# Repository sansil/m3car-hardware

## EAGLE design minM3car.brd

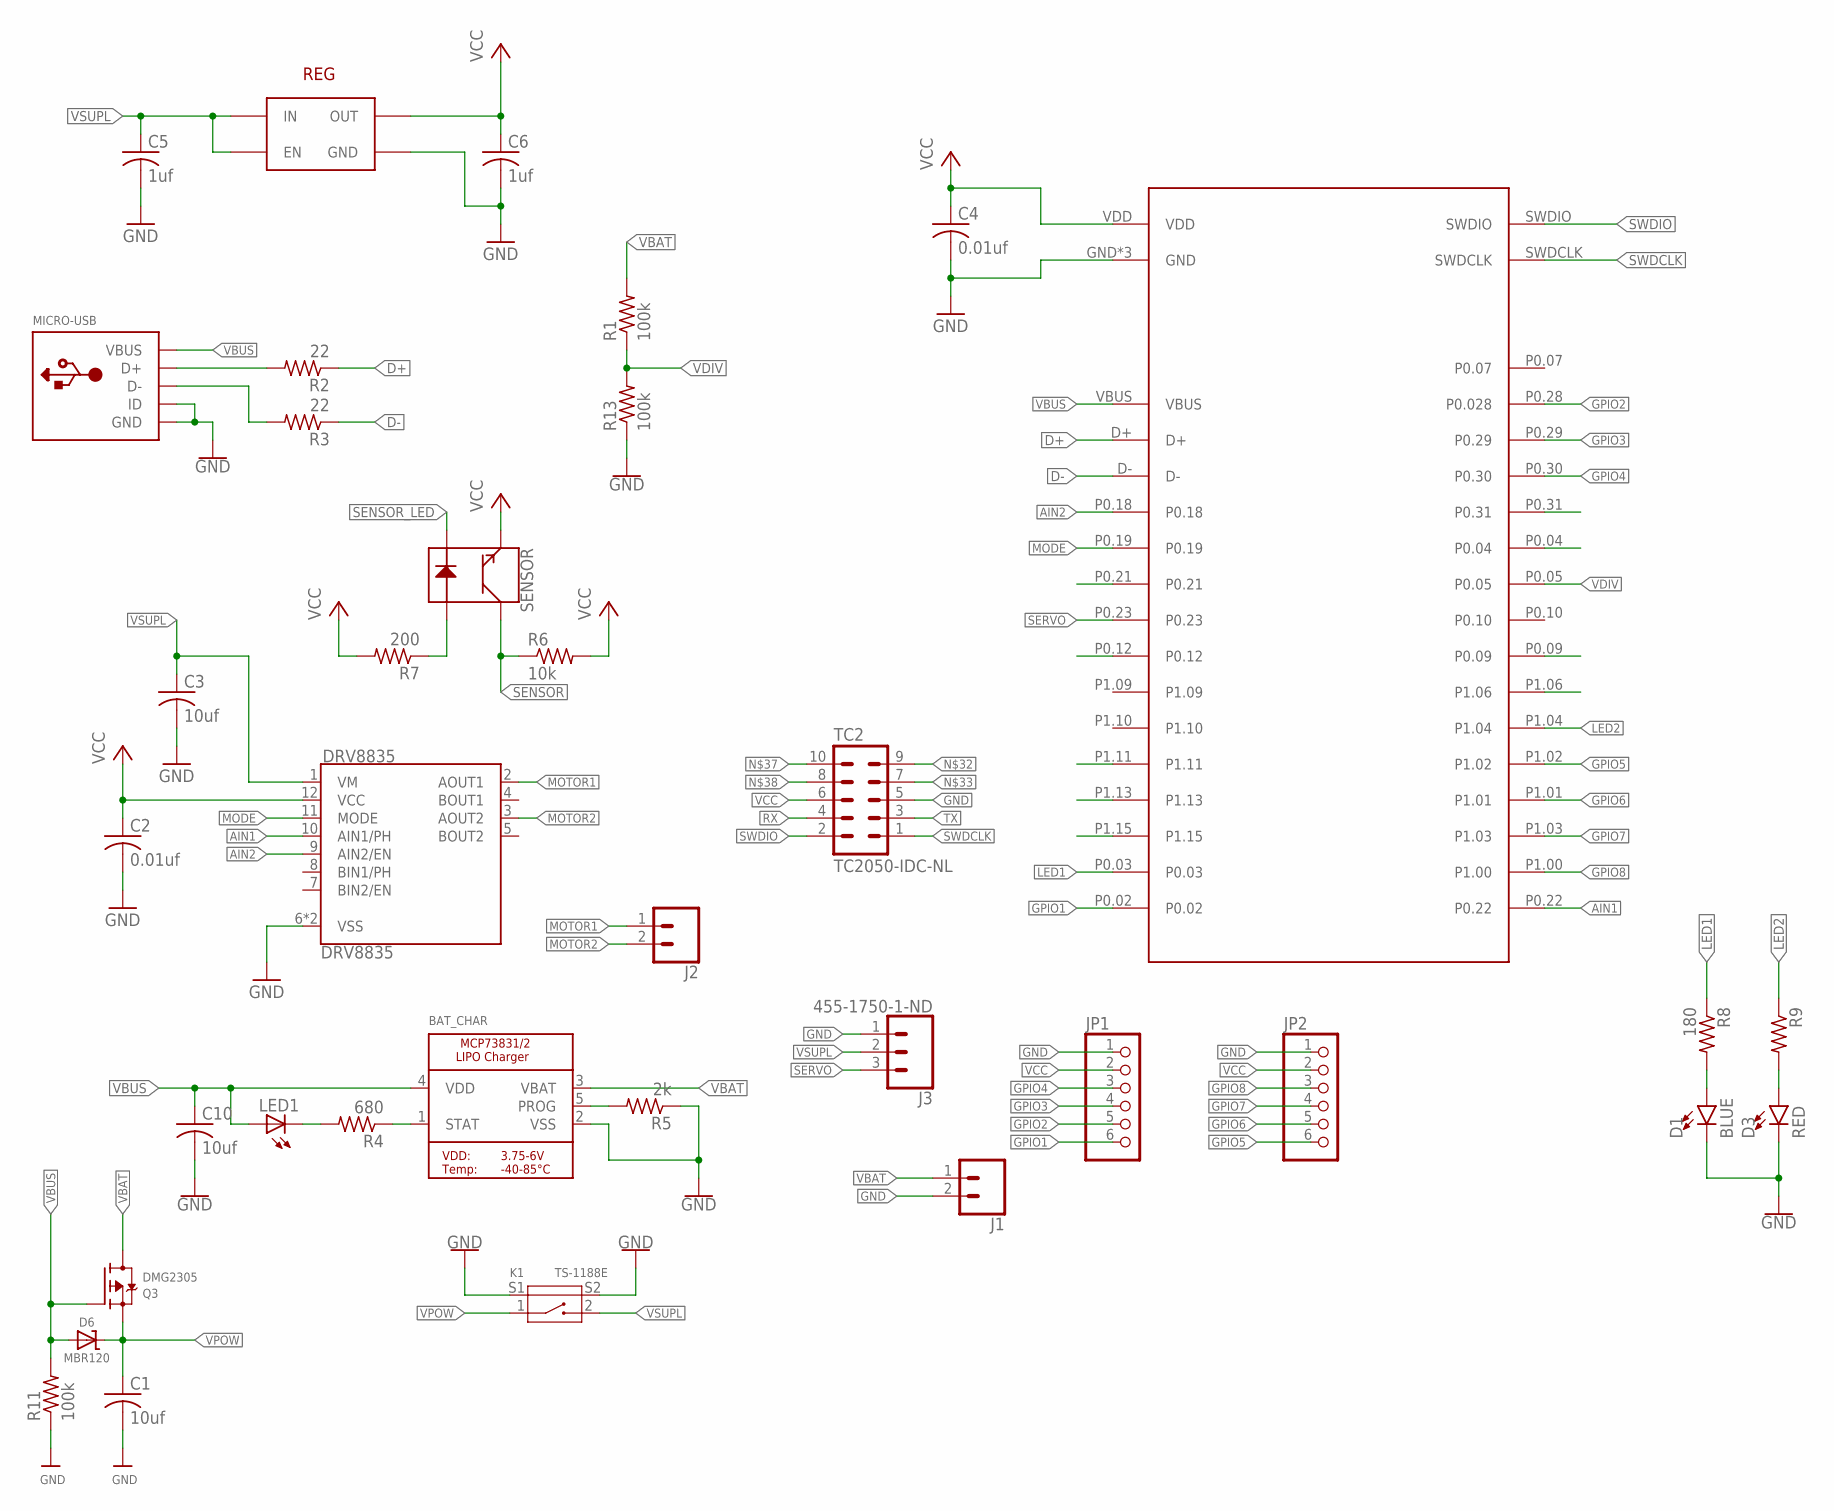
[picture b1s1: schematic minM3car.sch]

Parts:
BAT_CHAR: MICROBUILDER_MCP73831/2; MICROBUILDER_SOT23-5; MPN MCP73831T-2ACI/OT
C1, C3, C10: 10uf; C0402; MPN GRM155R60G106ME44D
C2, C4: 0.01uf; C0402; MPN CL05C100JB5NNNC
C5, C6: 1uf; C0402; MPN CL05A105KP5NNNC
D1: BLUE; LED-0603; MPN 150060YS75000
D3: RED; LED-0603; MPN 150060YS75000
D6: MBR120; SOD-123; MPN MBR120VLSFT3G
DRV8835: DRV8835; WSON-12; MPN DRV8835DSSR
J1, J2: CONN_02; 1X02
J3: 455-1750-1-ND; 1X03
JP1, JP2: PINHD-1X6; 1X06
K1: TS-1188E; SW4-SMD-7.0X3.5X3.5MM-90D
LED1: LEDCHIPLED_0603; CHIPLED_0603; MPN 150060GS75000
MICRO-USB: MICROBUILDER_USB_MICRO_20329_V2; MICROBUILDER_4UCONN_20329_V2; MPN 10103592-0001LF
NRF52: HOLYIOT; MPN 113990556
Q3: DMG2305; SOT23-R; MPN DMG2305UXQ-7
R1, R11, R13: 100k; R0402; MPN RC0402JR-07100KL
R2, R3: 22; R0402; MPN BLM15BB220SN1D
R4: 680; R0402; MPN RC0402JR-07680RL
R5: 2k; R0402; MPN RC0402FR-072KL
R6: 10k; R0402; MPN RC0402JR-0710KL
R7: 200; R0402; MPN 0402WGF2000TCE
R8, R9: 180; R0402; MPN RC0402FR-07180RL
REG: TLV703; SOT95P285X120-5N; MPN TLV7031DBVR
SENSOR: QRE1113SMD-W; QRE1113-W; MPN QRE1113GR
TC2: TC2050-IDC-NL

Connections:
AIN1: DRV8835.10 (AIN1/PH), NRF52.P0.22
AIN2: DRV8835.9 (AIN2/EN), NRF52.P0.18
D+: NRF52.D+, R2.1
D-: NRF52.D-, R3.1
GND: BAT_CHAR.2 (VSS), C1.2, C2.2, C3.2, C4.2, C5.2, C6.2, C10.2, D1.C, D3.C, DRV8835.6 (VSS), DRV8835.PAD (VSS), J1.2, J3.1, JP1.1, JP2.1, K1.S1, K1.S2, MICRO-USB.BASE@1 (GND), MICRO-USB.BASE@2 (GND), MICRO-USB.GND, MICRO-USB.ID, MICRO-USB.SPRT@1 (GND), MICRO-USB.SPRT@2 (GND), MICRO-USB.SPRT@3 (GND), MICRO-USB.SPRT@4 (GND), NRF52.GND, NRF52.GND2 (GND), NRF52.GND3 (GND), R5.1, R11.1, R13.1, REG.2 (GND), TC2.5
GPIO1: JP1.6, NRF52.P0.02
GPIO2: JP1.5, NRF52.P0.28 (P0.028)
GPIO3: JP1.4, NRF52.P0.29
GPIO4: JP1.3, NRF52.P0.30
GPIO5: JP2.6, NRF52.P1.02
GPIO6: JP2.5, NRF52.P1.01
GPIO7: JP2.4, NRF52.P1.03
GPIO8: JP2.3, NRF52.P1.00
LED1: NRF52.P0.03, R8.1
LED2: NRF52.P1.04, R9.1
MODE: DRV8835.11 (MODE), NRF52.P0.19
MOTOR1: DRV8835.2 (AOUT1), J2.1
MOTOR2: DRV8835.3 (AOUT2), J2.2
unnamed: D1.A, R8.2
unnamed: LED1.C, R4.2
unnamed: D3.A, R9.2
unnamed: MICRO-USB.D+, R2.2
unnamed: MICRO-USB.D-, R3.2
unnamed: R7.1, SENSOR.1 (A)
unnamed: BAT_CHAR.5 (PROG), R5.2
unnamed: BAT_CHAR.1 (STAT), R4.1
RX: TC2.4
SENSOR: R6.1, SENSOR.3 (C)
SENSOR_LED: SENSOR.2 (K)
SERVO: J3.3, NRF52.P0.23
SWDCLK: NRF52.SWDCLK, TC2.1
SWDIO: NRF52.SWDIO, TC2.2
TX: TC2.3
VBAT: BAT_CHAR.3 (VBAT), J1.1, Q3.3 (D), R1.2
VBUS: BAT_CHAR.4 (VDD), C10.1, D6.A, LED1.A, MICRO-USB.VBUS, NRF52.VBUS, Q3.1 (G), R11.2
VCC: C2.1, C4.1, C6.1, DRV8835.12 (VCC), JP1.2, JP2.2, NRF52.VDD, R6.2, R7.2, REG.5 (OUT), SENSOR.4 (E), TC2.6
VDIV: NRF52.P0.05, R1.1, R13.2
VPOW: C1.1, D6.C, K1.1, Q3.2 (S)
VSUPL: C3.1, C5.1, DRV8835.1 (VM), J3.2, K1.2, REG.1 (IN), REG.3 (EN)

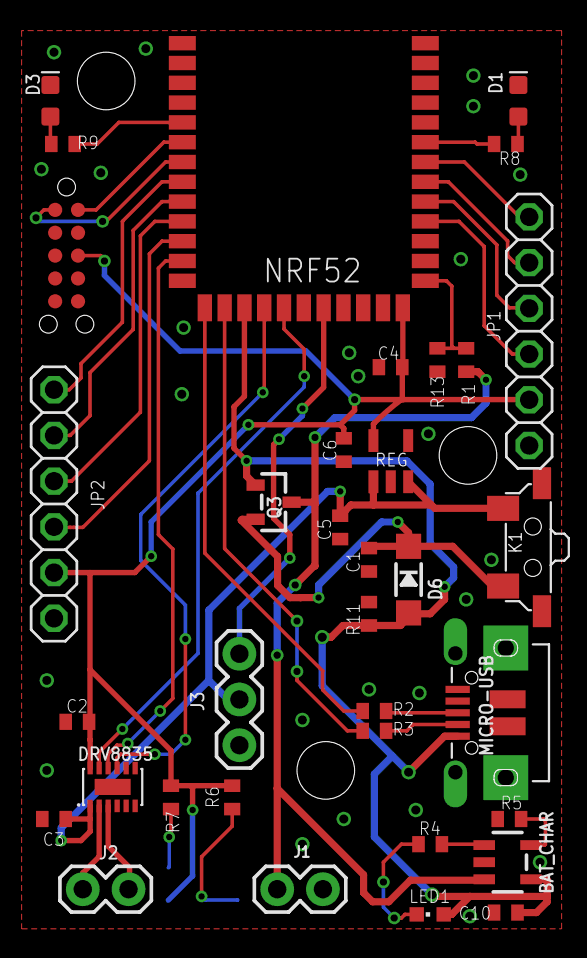
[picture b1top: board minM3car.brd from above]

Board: 2 copper layers, 36 parts (1 on the bottom side), 36 nets.

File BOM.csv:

"Qty";"Value";"Device";"Package";"Parts";"Description";"LINK";"MPN";"PROD_ID";"SF_ID";"VALUE";
"2";"";"CONN_02";"1X02";"J1, J2";"Multi connection point. Often used as Generic Header-pin footprint for 0.1 inch spaced/style header connections";"";"";"";"";"";
"1";"";"LEDCHIPLED_0603";"CHIPLED_0603";"LED1";"LED";"";"150060GS75000";"";"";"";
"1";"";"MICROBUILDER_MCP73831/2";"MICROBUILDER_SOT23-5";"BAT_CHAR";"MCP73831/2 LIPO Charger";"https://uy.mouser.com/ProductDetail/Microchip-Technology/MCP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";" MCP73831T-2ACI/OT";"";"";"";
"1";"";"MICROBUILDER_USB_MICRO_20329_V2";"MICROBUILDER_4UCONN_20329_V2";"MICRO-USB";"USB Connectors";"https://www.digikey.com/product-detail/en/amphenol-icc-fci/1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";"10103592-0001LF ";"";"";"";
"2";"";"PINHD-1X6";"1X06";"JP1, JP2";"PIN HEADER";"";"";"";"";"";
"1";"";"QRE1113SMD-W";"QRE1113-W";"SENSOR";"QRE1113 Reflective Object Sensor";"https://uy.mouser.com/ProductDetail/ON-Semiconductor-Fairchi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";"QRE1113GR";"IC-09357";"COM-09542";"";
"2";"0.01uf";"C-USC0402";"C0402";"C2, C4";"CAPACITOR, American symbol";"";"CL05C100JB5NNNC";"";"";"";
"3";"100k";"R-US_R0402";"R0402";"R1, R11, R13";"RESISTOR, American symbol";"";"RC0402JR-07100KL";"";"";"";
"1";"10k";"R-US_R0402";"R0402";"R6";"RESISTOR, American symbol";"https://www.seeedstudio.com/opl.html";"RC0402JR-0710KL";"";"";"";
"3";"10uf";"C-USC0402";"C0402";"C1, C3, C10";"CAPACITOR, American symbol";"";"GRM155R60G106ME44D";"";"";"";
"2";"180";"R-US_R0402";"R0402";"R8, R9";"RESISTOR, American symbol";"https://www.seeedstudio.com/opl.html";"RC0402FR-07180RL";"";"";"";
"2";"1uf";"C-USC0402";"C0402";"C5, C6";"CAPACITOR, American symbol";"";"CL05A105KP5NNNC";"";"";"";
"1";"200";"R-US_R0402";"R0402";"R7";"RESISTOR, American symbol";"";"0402WGF2000TCE";"";"";"";
"2";"22";"R-US_R0402";"R0402";"R2, R3";"RESISTOR, American symbol";"https://www.seeedstudio.com/opl.html";"BLM15BB220SN1D";"";"";"";
"1";"2k";"R-US_R0402";"R0402";"R5";"RESISTOR, American symbol";"";"RC0402FR-072KL";"";"";"";
"1";"455-1750-1-ND";"CONN_03";"1X03";"J3";"Multi connection point. Often used as Generic Header-pin footprint for 0.1 inch spaced/style header connections";"";"";"XXX-00000";"";"455-1750-1-ND";
"1";"680";"R-US_R0402";"R0402";"R4";"RESISTOR, American symbol";"https://www.seeedstudio.com/opl.html";"RC0402JR-07680RL";"";"";"";
"1";"BLUE";"LED-BLUE0603";"LED-0603";"D1";"Blue SMD LED";"";"150060YS75000";"DIO-08575";"";"BLUE";
"1";"DMG2305";"MOSFET-P";"SOT23-R";"Q3";"P-Channel Mosfet";"";"DMG2305UXQ-7";"";"";"";
"1";"DRV8835";"DRV883X";"WSON-12";"DRV8835";"DRV8835 2 Channel Motor Driver";"https://uy.mouser.com/ProductDetail/Texas-Instruments/DRV883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";"DRV8835DSSR";"IC-13342";"";"DRV8835";
"1";"HOLYIOT";"HOLYIOT";"HOLYIOT";"NRF52";"";"";"113990556";"";"";"";
"1";"MBR120";"DIODE-SCHOTTKYSOD-123";"SOD-123";"D6";"";"";"MBR120VLSFT3G";"";"";"";
"1";"RED";"LED-RED0603";"LED-0603";"D3";"Red SMD LED";"";"150060YS75000";"DIO-00819";"";"RED";
"1";"TC2050-IDC-NL";"TC2050-IDC-NL";"TC2050-IDC-NL";"TC2";"Tag-Connect In Circuit Programming & Debug Cable 10 Pin";"";"";"";"";"";
"1";"TLV703";"TLV703";"SOT95P285X120-5N";"REG";"";"https://uy.mouser.com/ProductDetail/Texas-Instruments/TLV703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";"TLV7031DBVR";"";"";"";
"1";"TS-1188E";"SMD-BUTTON(2+2P-7X3.5MM-90D)";"SW4-SMD-7.0X3.5X3.5MM-90D";"K1";"311020023";"";"TS-1188E";"";"";"TS-1188E";

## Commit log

2019-07-02 avance
2019-07-02 nuevo avance
2019-07-04 agrego mpn
2019-07-04 placa sin boton
2019-07-05 placa finalizada
2019-07-26 assemby drawing

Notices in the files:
parts and their libraries:
SparkFun-Sensors: Licensing: Creative Commons ShareAlike 4.0 International - https://creativecommons.org/licenses/by-sa/4.0
microbuilder: This work is placed in the public domain, and may be freely used for commercial and non-commercial work with the following conditions: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
